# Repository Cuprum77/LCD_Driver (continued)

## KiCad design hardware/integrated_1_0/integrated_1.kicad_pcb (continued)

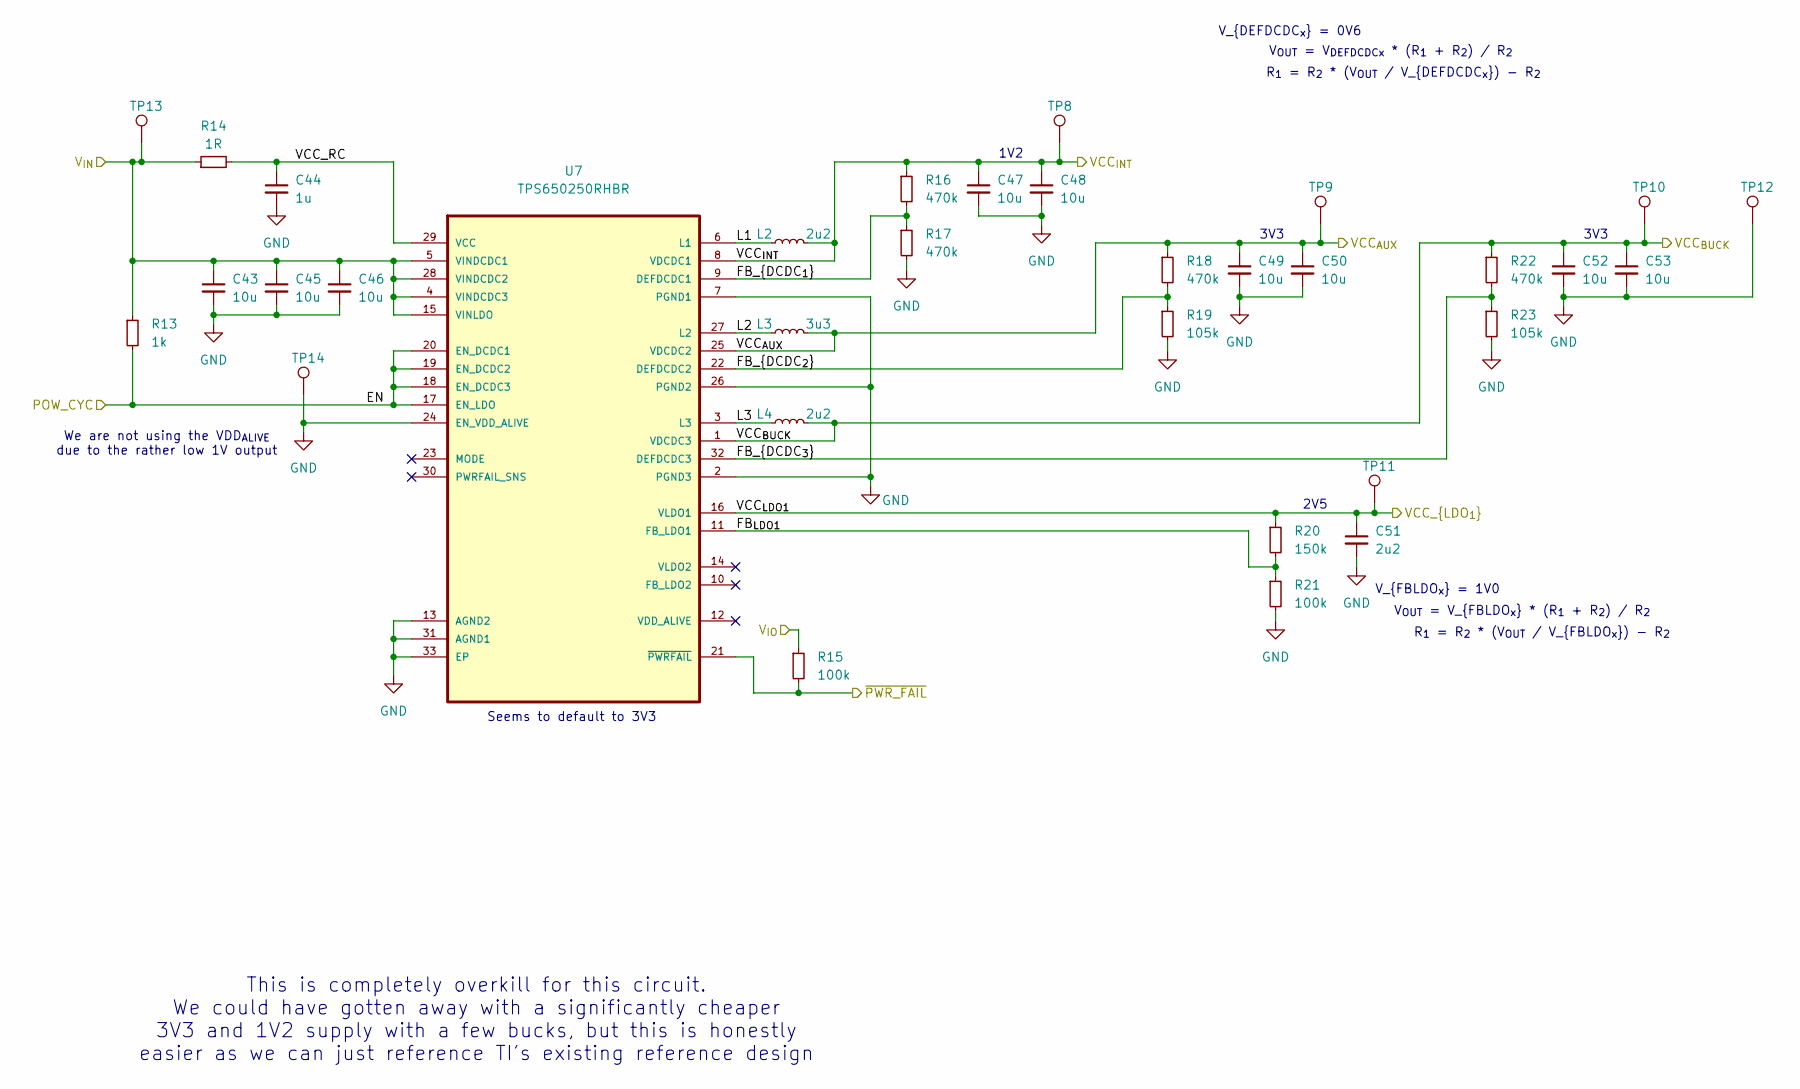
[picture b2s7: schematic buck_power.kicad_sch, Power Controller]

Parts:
C43, C45, C46, C47, C48, C49, C50, C52, C53: 10u; C_0603_1608Metric
C44: 1u; C_0402_1005Metric
C51: 2u2; C_0603_1608Metric
L2, L4: 2u2; XRNR4012
L3: 3u3; XRNR4012
R13: 1k; R_0402_1005Metric
R14: 1R; R_0402_1005Metric
R15, R21: 100k; R_0402_1005Metric
R16, R17, R18, R22: 470k; R_0402_1005Metric
R19, R23: 105k; R_0402_1005Metric
R20: 150k; R_0402_1005Metric
TP8, TP9, TP10, TP11, TP12, TP13, TP14: TestPoint; TestPoint_Pad_D1.0mm
U7: TPS650250RHBR; IC_ADS125H01IRHBT

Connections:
+2V5: C51.1, R20.1, TP11.1, U7.16 (VLDO1); also elsewhere on the board
+3V3: C52.1, C53.1, L4.2, R15.1, R22.1, TP10.1, U7.1 (VDCDC3); also elsewhere on the board
+5V: C43.1, C45.1, C46.1, R13.1, R14.1, TP13.1, U7.4 (VINDCDC3), U7.5 (VINDCDC1), U7.15 (VINLDO), U7.28 (VINDCDC2); also elsewhere on the board
/Buck Converter/EN: R13.2, U7.17 (EN_LDO), U7.18 (EN_DCDC3), U7.19 (EN_DCDC2), U7.20 (EN_DCDC1); also elsewhere on the board
/Buck Converter/FB_{DCDC_{1}}: R16.2, R17.1, U7.9 (DEFDCDC1)
/Buck Converter/FB_{DCDC_{2}}: R18.2, R19.1, U7.22 (DEFDCDC2)
/Buck Converter/FB_{DCDC_{3}}: R22.2, R23.1, U7.32 (DEFDCDC3)
/Buck Converter/FB_{LDO1}: R20.2, R21.1, U7.11 (FB_LDO1)
/Buck Converter/L1: L2.1, U7.6 (L1)
/Buck Converter/L2: L3.1, U7.27 (L2)
/Buck Converter/L3: L4.1, U7.3 (L3)
/Buck Converter/VCC_RC: C44.1, R14.2, U7.29 (VCC)
/Buck Converter/~PWR_FAIL: R15.2, U7.21 (~PWRFAIL); also elsewhere on the board
/VCC_{AUX}: C49.1, C50.1, L3.2, R18.1, TP9.1, U7.25 (VDCDC2); also elsewhere on the board
/VCC_{INT}: C47.1, C48.1, L2.2, R16.1, TP8.1, U7.8 (VDCDC1); also elsewhere on the board
GND: C43.2, C44.2, C45.2, C46.2, C47.2, C48.2, C49.2, C50.2, C51.2, C52.2, C53.2, R17.2, R19.2, R21.2, R23.2, TP12.1, TP14.1, U7.2 (PGND3), U7.7 (PGND1), U7.13 (AGND2), U7.24 (EN_VDD_ALIVE), U7.26 (PGND2), U7.31 (AGND1), U7.33 (EP), U7.34 (EP), U7.35 (EP), U7.36 (EP), U7.37 (EP), U7.38 (EP); also elsewhere on the board

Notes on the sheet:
V_{DEFDCDC_{x}} = 0V6
Seems to default to 3V3
R_{1} = R_{2} * (V_{OUT} / V_{DEFDCDC_{x}}) - R_{2}
3V3
2V5
V_{FBLDO_{x}} = 1V0
V_{OUT} = V_{FBLDO_{x}} * (R_{1} + R_{2}) / R_{2}
This is completely overkill for this circuit. We could have gotten away with a significantly cheaper 3V3 and 1V2 supply with a few bucks, but this is honestly easier as we can just reference TI's existing reference design
R_{1} = R_{2} * (V_{OUT} / V_{FBLDO_{x}}) - R_{2}
V_{OUT} = V_{DEFDCDCx} * (R_{1} + R_{2}) / R_{2}
We are not using the VDD_{ALIVE} due to the rather low 1V output
3V3
1V2

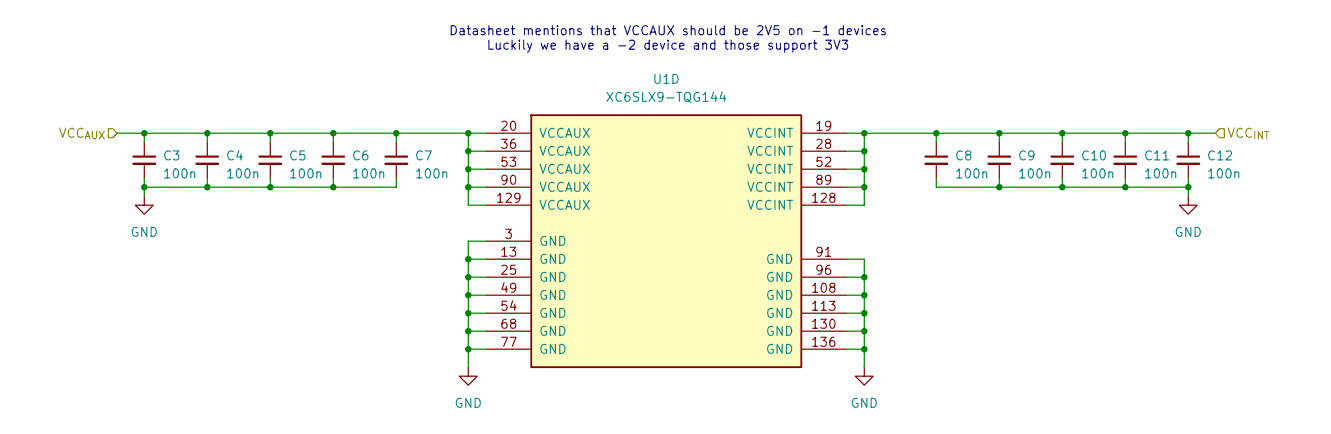
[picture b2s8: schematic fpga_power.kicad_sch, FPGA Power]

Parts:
C3, C4, C5, C6, C7, C8, C9, C10, C11, C12: 100n; C_0402_1005Metric
U1: XC6SLX9-TQG144; TQFP-144_20x20mm_P0.5mm

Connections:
/VCC_{AUX}: C8.1, C9.1, C10.1, C11.1, C12.1, U1.19 (VCCINT), U1.28 (VCCINT), U1.52 (VCCINT), U1.89 (VCCINT), U1.128 (VCCINT); also elsewhere on the board
/VCC_{INT}: C3.1, C4.1, C5.1, C6.1, C7.1, U1.20 (VCCAUX), U1.36 (VCCAUX), U1.53 (VCCAUX), U1.90 (VCCAUX), U1.129 (VCCAUX); also elsewhere on the board
GND: C3.2, C4.2, C5.2, C6.2, C7.2, C8.2, C9.2, C10.2, C11.2, C12.2, U1.3 (GND), U1.13 (GND), U1.25 (GND), U1.49 (GND), U1.54 (GND), U1.68 (GND), U1.77 (GND), U1.91 (GND), U1.96 (GND), U1.108 (GND), U1.113 (GND), U1.130 (GND), U1.136 (GND); also elsewhere on the board

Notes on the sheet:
Datasheet mentions that VCCAUX should be 2V5 on -1 devices Luckily we have a -2 device and those support 3V3

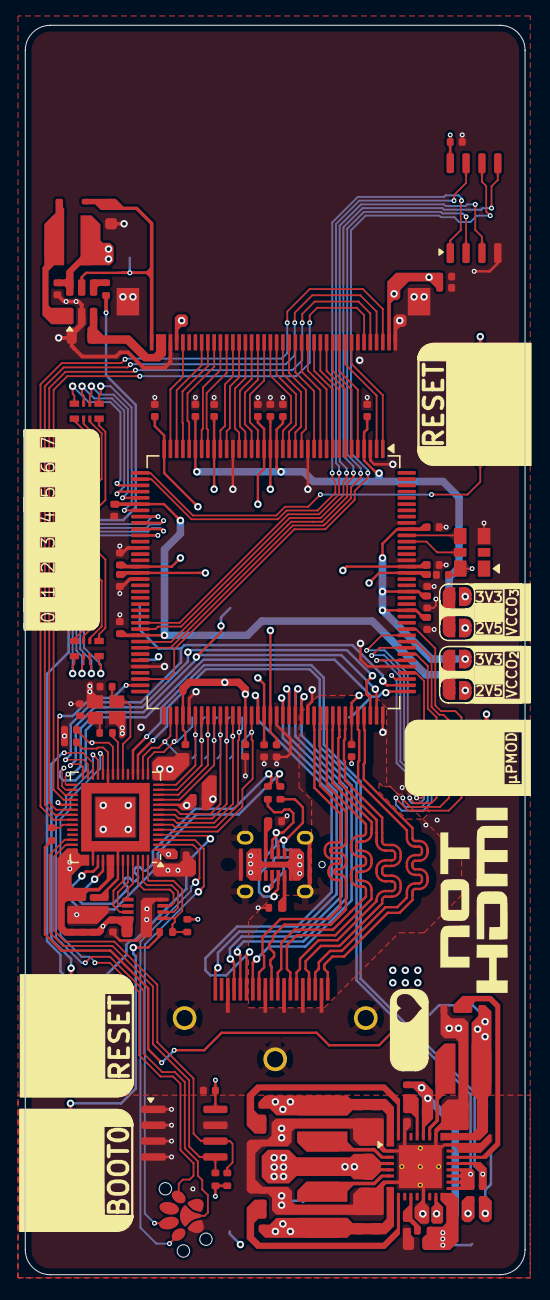
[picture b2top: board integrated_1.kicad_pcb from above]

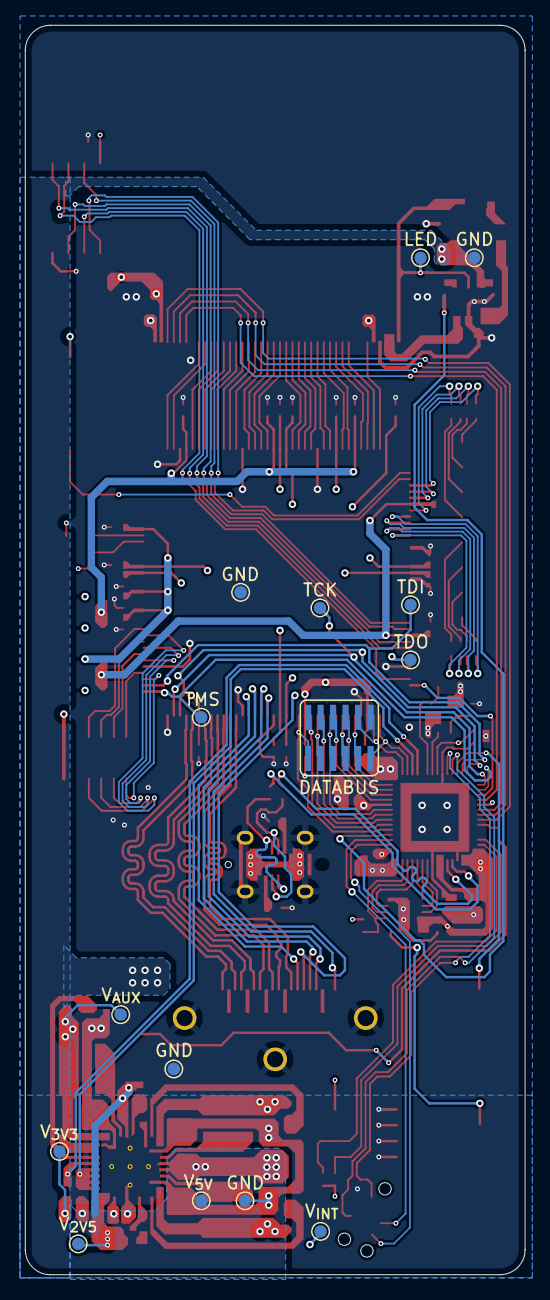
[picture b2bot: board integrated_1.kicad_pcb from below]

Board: 4 copper layers, 40.0 x 100.0 mm, 129 parts (15 on the bottom side), 141 nets.

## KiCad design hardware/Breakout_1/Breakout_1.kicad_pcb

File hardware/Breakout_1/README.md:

# Breakout Board
Note, this is not a complete project. It lacks the necessary files to properly modify the design. This is purely out of the fact that this is a prototype and I am too lazy to properly document it.

This repo contains the KiCAD files for the first iteration of this project, the breakout board.

## Known Issues

These are the known issues with the current design:
- No pull-up resistors on the I2C lines
- No reset button
- No ability to power the board from the USB port (for the microcontroller)
- Difficult to add external power to the board
- More ground connections!
- Boost Converter is not capable of providing enough current for the display. Does not match the chips rated output.

## 3D Files

In the [3D](./3d/) folder you can find the 3D models for the board and a stand for the display to rest on.
The [stand](./3d/stand.stl) is a very crude design. It may not be very printable, but it works well enough for a prototype. 

This will not be developed further as there will not be a need for it in the final design.

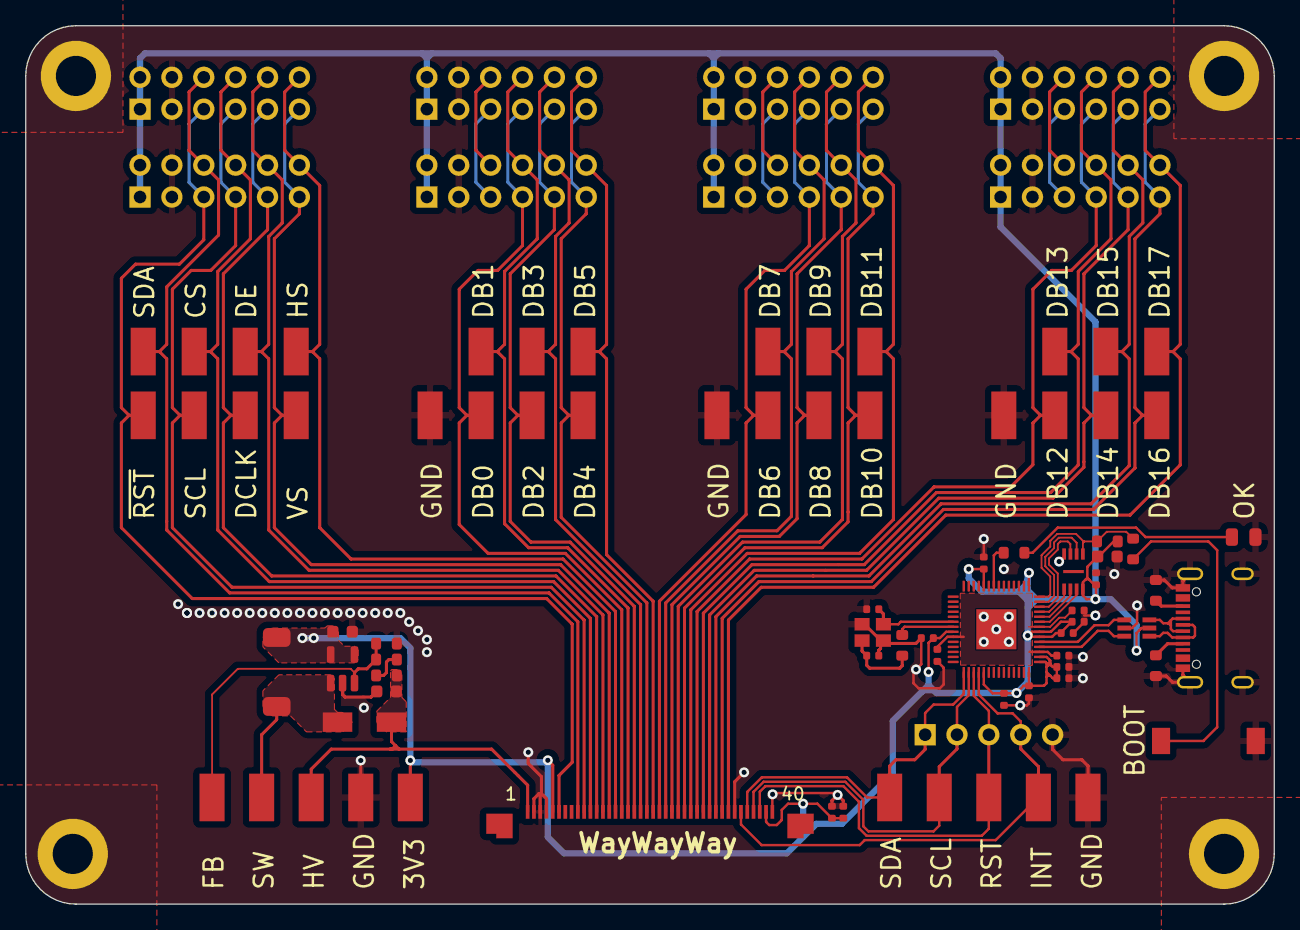
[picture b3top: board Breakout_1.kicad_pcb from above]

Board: 2 copper layers, 99.5 x 70.0 mm, 87 parts (0 on the bottom side), 61 nets.

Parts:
C1, C12, C22: 1u; C_0402_1005Metric
C2, C6, C9, C10, C13, C14, C15, C16, C17, C18, C19: 100n; C_0402_1005Metric
C3: 1u; C_0603_1608Metric
C4, C5: 8p; C_0402_1005Metric
C7: 10u; C_0603_1608Metric
C8: 2u2; C_0603_1608Metric
D1: LED; D_0805_2012Metric
D2: SS14; DIOM5227X270N
DS1: ST7701_IPS_3.99_TOUCH; AMPHENOL_F32Q-1A7H1-11040
J1, J2, J3, J4: Conn_01x12; PinHeader_2x06_P2.54mm_Horizontal
J5, J6, J7, J8: Conn_01x12; PinHeader_2x06_P2.54mm_Vertical
J9: USB4105-GF-A-120; USB_C_Receptacle_GCT_USB4105-xx-A_16P_TopMnt_Horizontal
J10: Conn_01x05; PinHeader_1x05_P2.54mm_Vertical
L1: 10u; L_TDK_SLF6045
R1, R2: 5k1; R_0603_1608Metric
R3: 270; R_0603_1608Metric
R4: 10K; R_0603_1608Metric
R5: DNF; R_0603_1608Metric
R6: 1k; R_0603_1608Metric
R7, R9: 1M; R_0603_1608Metric
R8: 105k; R_0603_1608Metric
SW1: DNF; PTS636 SM25J SMTR LFS
TP1, TP4, TP5, TP6, TP7, TP8, TP9, TP10, TP11, TP12, TP13, TP14, TP15, TP16, TP17, TP18, TP19, TP20, TP21, TP22, TP23, TP24, TP25, TP26, TP27, TP28, TP29, TP30, TP31, TP32, TP33, TP34, TP35, TP36, TP37, TP38, TP39, TP40, TP41: TestPoint; TestPoint_Keystone_5019_Minature_No_Silkscreen
U1: AP3015; SOT-23-5
U2: W25Q16JV; W25Q16JVUXIQ TR
U3: USBUF02W6; SOT65P210X110-6N
U4: RP2040; QFN-56-1EP_7x7mm_P0.4mm_EP3.2x3.2mm
Y1: 12MHz; ECS120836CKMTR3

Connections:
+1V1: C9.1, C10.1, C12.1, U4.23 (DVDD), U4.45 (VREG_VOUT), U4.50 (DVDD)
+3V3: C1.1, C2.1, C6.1, C7.1, C8.1, C13.1, C14.1, C15.1, C16.1, C17.1, C18.1, C19.1, C22.1, DS1.5 (VCC), DS1.39 (TP_VCC), J1.1, J1.2, J2.1, J2.2, J3.1, J3.2, J4.1, J4.2, J5.1, J5.2, J6.1, J6.2, J7.1, J7.2, J8.1, J8.2, L1.1, R5.2, TP34.1, U1.4 (~SHDN), U1.5 (VIN), U2.8 (VCC), U3.5 (3V3), U4.1 (IOVDD), U4.10 (IOVDD), U4.22 (IOVDD), U4.33 (IOVDD), U4.42 (IOVDD), U4.43 (ADC_AVDD), U4.44 (VREG_IN), U4.48 (USB_VDD), U4.49 (IOVDD)
/CS: DS1.11 (CS), J1.8, J5.8, TP7.1
/DB0: DS1.16 (DB0), J2.7, J6.7, TP12.1
/DB1: DS1.17 (DB1), J2.8, J6.8, TP13.1
/DB2: DS1.18 (DB2), J2.9, J6.9, TP14.1
/DB3: DS1.19 (DB3), J2.10, J6.10, TP15.1
/DB4: DS1.20 (DB4), J2.11, J6.11, TP16.1
/DB5: DS1.21 (DB5), J2.12, J6.12, TP17.1
/DB6: DS1.22 (DB6), J3.7, J7.7, TP18.1
/DB7: DS1.23 (DB7), J3.8, J7.8, TP19.1
/DB8: DS1.24 (DB8), J3.9, J7.9, TP20.1
/DB9: DS1.25 (DB9), J3.10, J7.10, TP21.1
/DB10: DS1.26 (DB10), J3.11, J7.11, TP22.1
/DB11: DS1.27 (DB11), J3.12, J7.12, TP23.1
/DB12: DS1.28 (DB12), J4.7, J8.7, TP24.1
/DB13: DS1.29 (DB13), J4.8, J8.8, TP25.1
/DB14: DS1.30 (DB14), J4.9, J8.9, TP26.1
/DB15: DS1.31 (DB15), J4.10, J8.10, TP27.1
/DB16: DS1.32 (DB16), J4.11, J8.11, TP28.1
/DB17: DS1.33 (DB17), J4.12, J8.12, TP29.1
/DCLK: DS1.12 (DCLK), J1.9, J5.9, TP8.1
/DE: DS1.13 (DE), J1.10, J5.10, TP9.1
/FB: R8.1, R9.2, TP40.1, U1.3 (FB)
/HS: DS1.15 (HS), J1.12, J5.12, TP11.1
/LEDA: C3.1, D2.1 (K), DS1.1 (LEDA), R7.1, TP1.1
/Microcontroller/LED_STATUS: R3.2, U4.8 (GPIO6)
/Microcontroller/QSPI_SCLK: U2.6 (CLK), U4.52 (QSPI_SCLK)
/Microcontroller/QSPI_SD0: U2.5 (DI(IO0)), U4.53 (QSPI_SD0)
/Microcontroller/QSPI_SD1: U2.2 (DO(IO1)), U4.55 (QSPI_SD1)
/Microcontroller/QSPI_SD2: U2.3 (IO2), U4.54 (QSPI_SD2)
/Microcontroller/QSPI_SD3: U2.7 (IO3), U4.51 (QSPI_SD3)
/Microcontroller/QSPI_SS: R4.1, R5.1, U2.1 (~CS), U4.56 (QSPI_SS)
/Microcontroller/USB_D+: U3.1 (D+), U4.47 (USB_DP)
/Microcontroller/USB_D-: U3.3 (D-), U4.46 (USB_DM)
/Microcontroller/USB_DR+: J9.A6 (D+), J9.B6 (D+), U3.6 (D+)
/Microcontroller/USB_DR-: J9.A7 (D-), J9.B7 (D-), U3.4 (D-)
/Microcontroller/XIN: C4.2, U4.20 (XIN), Y1.1
/Microcontroller/XOUT: R6.1, U4.21 (XOUT)
/Microcontroller/XOUT_R: C5.2, R6.2, Y1.3
/SCL: DS1.10 (SCL), J1.7, J5.7, TP6.1
/SDA: DS1.9 (SDA), J1.6, J5.6, TP5.1
/SWITCH: D2.2 (A), L1.2, TP41.1, U1.1 (SW)
/TP_INT: DS1.35 (TP_INT), J10.4, TP30.1, U4.32 (GPIO21)
/TP_RST: DS1.38 (TP_RST), J10.3, TP33.1, U4.31 (GPIO20)
/TP_SCL: DS1.37 (TP_SCL), J10.2, TP32.1, U4.30 (GPIO19)
/TP_SDA: DS1.36 (TP_SDA), J10.1, TP31.1, U4.29 (GPIO18)
/VS: DS1.14 (VS), J1.11, J5.11, TP10.1
/~RST: DS1.6 (~RST), J1.5, J5.5, TP4.1
GND: C1.2, C2.2, C3.2, C4.1, C5.1, C6.2, C7.2, C8.2, C9.2, C10.2, C12.2, C13.2, C14.2, C15.2, C16.2, C17.2, C18.2, C19.2, C22.2, D1.1 (K), DS1.2 (LEDK1), DS1.3 (LEDK2), DS1.4 (GND), DS1.34 (GND), DS1.40 (GND), J1.3, J1.4, J2.3, J2.4, J3.3, J3.4, J4.3, J4.4, J5.3, J5.4, J6.3, J6.4, J7.3, J7.4, J8.3, J8.4, J9.A1 (GND), J9.A12 (GND), J9.B1 (GND), J9.B12 (GND), J9.S1 (SHIELD), J10.5, R1.1, R2.1, R8.2, SW1.1, TP35.1, TP36.1, TP37.1, TP38.1, TP39.1, U1.2 (GND), U2.4 (GND), U3.2 (Grd), U4.57 (GND), Y1.2, Y1.4
unnamed: D1.2 (A), R3.1
unnamed: J2.5, J6.5
unnamed: J2.6, J6.6
unnamed: J3.5, J7.5
unnamed: J3.6, J7.6
unnamed: J4.5, J8.5
unnamed: J4.6, J8.6
unnamed: J9.A5 (CC1), R1.2
unnamed: J9.B5 (CC2), R2.2
unnamed: R4.2, SW1.2
unnamed: R7.2, R9.1

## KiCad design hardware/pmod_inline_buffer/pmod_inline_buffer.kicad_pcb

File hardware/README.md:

# Hardware

This repo contains the KiCAD files for the current hardware prototypes of the LCD driver board.

## Current version

The latest board manufactured is the [Breakout_1](Breakout_1/) board. This PCB is a breakout board for the LCD display, which allows for easy testing and verification of the display. It also contains a 40 pin header for the LCD display itself and a PMOD interface for hooking up with a FPGA board.

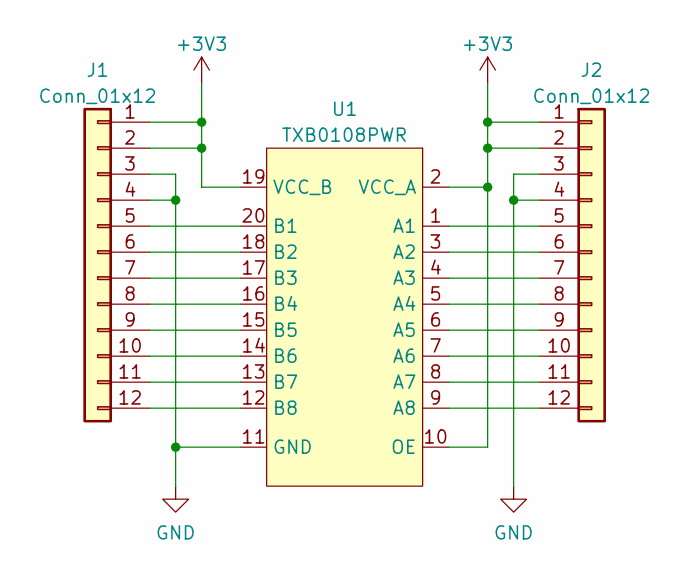
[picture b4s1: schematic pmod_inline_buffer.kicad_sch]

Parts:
J1: Conn_01x12; PinHeader_2x06_P2.54mm_Horizontal
J2: Conn_01x12; PinSocket_2x06_P2.54mm_Horizontal
U1: TXB0108PWR; TSSOP-20_4.4x6.5mm_P0.65mm

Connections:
+3V3: J1.1, J1.2, J2.1, J2.2, U1.2 (VCC_A), U1.10 (OE), U1.19 (VCC_B)
GND: J1.3, J1.4, J2.3, J2.4, U1.11 (GND)
unnamed: J1.5, U1.20 (B1)
unnamed: J1.6, U1.18 (B2)
unnamed: J1.7, U1.17 (B3)
unnamed: J1.8, U1.16 (B4)
unnamed: J1.9, U1.15 (B5)
unnamed: J1.10, U1.14 (B6)
unnamed: J1.11, U1.13 (B7)
unnamed: J1.12, U1.12 (B8)
unnamed: J2.5, U1.1 (A1)
unnamed: J2.6, U1.3 (A2)
unnamed: J2.7, U1.4 (A3)
unnamed: J2.8, U1.5 (A4)
unnamed: J2.9, U1.6 (A5)
unnamed: J2.10, U1.7 (A6)
unnamed: J2.11, U1.8 (A7)
unnamed: J2.12, U1.9 (A8)

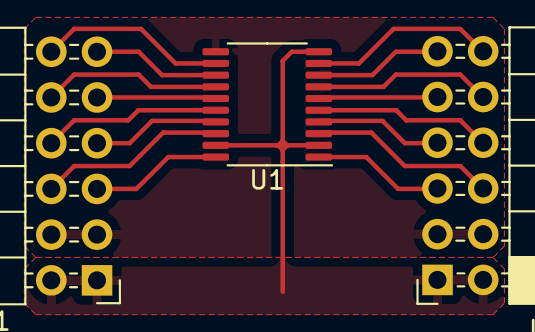
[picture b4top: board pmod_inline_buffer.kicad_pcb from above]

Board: 2 copper layers, 3 parts (0 on the bottom side), 18 nets.

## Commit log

2024-01-05 added gitignore
2024-01-05 first breakout board
2024-01-05 regenerated the gerber
2024-01-06 added license and a basic readme
2024-01-06 fixed readme?
2024-01-06 updated git ignore
2024-01-08 added a firmware folder
2024-01-08 added an ibom for breakout1
2024-01-08 spi hardware
2024-01-08 updated the spi to follow university guidelines
2024-01-08 added readme
2024-01-08 fixed some minor typos
2024-01-08 added the assembler for the psuedo assembly code
2024-01-08 updated the main readme
2024-01-08 updated the spi readme with docs
2024-01-08 typo
2024-01-08 improved readability
2024-01-08 simplified the instructionset
2024-01-08 fixed an error in overflow conditions
2024-01-09 fixed the output not taking comments into account
2024-01-09 added the sequencer
2024-01-09 fixed issue with rom and made it more efficient
2024-01-09 fixed a few names
2024-01-09 attempt to remove linguist from picking up ibom
2024-01-09 fixed flaw in readme, added example file
2024-01-09 updated the readme to reflect current state
2024-01-09 removed instructions from showing up, as this is supposed to be a general purpose module
2024-01-09 added a done signal for the top level
2024-01-09 moved the example instruction set to a dedicated folder
2024-01-09 updated readme to reflect changes
2024-01-09 added a missing newline (cosmetics)
2024-01-14 added uvvm as submodule
2024-01-14 replaced uvvm with uvvm_light
2024-01-14 added more readme files
2024-01-14 added simple readme for spi_init tb's
2024-01-14 added compiled uvvm folder gitignore
2024-01-14 added the rgb file with entity only
2024-01-14 added the spi simulation files
2024-01-14 fixed variable names not matching after previous update
2024-01-14 updated the main readme to include the new folders
2024-01-14 fixed bad link
2024-01-14 added the SPI UVVM testbench and relevant files
2024-01-14 updated testbench readmes
2024-01-14 fixed error in the readme
2024-01-14 removed unecessary words
2024-01-14 added default states to avoid simulation problems
2024-01-14 added the sequencer simulation files
2024-01-14 added the new sequencer testbench
2024-01-14 minor corrections of the spi simulation
2024-01-14 saving state
2024-01-14 restructured the project
2024-01-14 rewrote script to work in terminal
2024-01-14 removed unused files
2024-01-14 re-included accidently removed uvvm_light
2024-01-14 further restructuring
2024-01-14 correcting a typo
2024-01-14 removed unecessary files
2024-01-14 fixing wrong case leftover from restructuring
2024-01-14 updated the readme's to reflect changes
2024-01-14 updated more files to match the lowercase structure
2024-01-14 fixed the gitignore
2024-01-14 added known issues to the pcb page
2024-01-14 added information for the chipset used for touch
2024-01-14 added minimally functional library
2024-01-15 added rgb file
2024-01-15 added the top file
2024-01-15 minor spelling mistakes
2024-01-15 fixed a few things and added the sim file
2024-01-15 added a brief description to the RGB controller simulation
2024-01-15 fixed minor bugs
2024-01-16 added a resetter module
2024-01-16 updated project to reflect addition of resetter module
2024-01-16 added vivado project
2024-01-16 attempt 2 at the instructions
2024-01-16 added the ability to reset the heart
2024-01-16 gave the top a new heart
2024-01-16 updated formatting to match rest of project
2024-01-16 updated to make it not count generated hdl files
2024-01-16 updated to ignore all generated files (hopefully)
2024-01-16 updated again
2024-01-16 more readmes
2024-01-17 added an alternative d/c mode
2024-01-17 added the alternative d/c mode to the sequencer
2024-01-17 lowercase name
2024-01-17 crude start
2024-01-17 fixed minor typo
2024-01-21 added ability to invert the D/C bit from top-level
2024-01-21 re-ran the synthesis
2024-01-21 appended readme
2024-01-21 fixed a bad link
2024-01-21 passed variables up, fixed de signal fault
2024-01-21 updated tb to reflect changes
2024-01-21 updated top file to reflect changes, added a simple test pattern
2024-01-21 minor changes
2024-01-21 added digilent repo as a submodule
2024-01-21 fixed a spelling mistake
2024-01-21 fixed the naming in the uvvm code
2024-01-21 modified top to accept hdmi
2024-01-21 generic xilinx trash
2024-01-21 rgb sim rerun (new file)
2024-01-22 reverted to integrated ddc for the time being
2024-01-22 regenerated files
2024-01-22 added ddc files
2024-01-22 removed ddc, didnt work as hoped
2024-01-22 functional hdmi prototype
2024-01-23 cleanup, removed unused variables
2024-01-26 added the edid data needed to make it plug'n'play
2024-01-26 replaced bad link
2024-01-26 rewritten for consistency
2024-01-26 fixed spaces
2024-01-26 created a step file
2024-01-26 added the stand model
2024-01-26 renamed the folder to fit the restructuring (part 2)
2024-01-26 removed old folder
2024-01-26 updated the zybo readme
2024-01-26 updated the readme to reflect changes
2024-01-27 temporarily ignore doxy files
2024-01-27 moved the rom generator
2024-01-27 moved the rom generator and rewrote the python script
2024-01-27 removed to-be-rewritten files
2024-01-27 moved the datasheets
2024-01-27 removed unused code
2024-01-27 moved the software files
2024-01-27 added work in progress files
2024-01-27 renamed the simulation folder to match project layout
2024-01-27 crude update of main readme
2024-01-27 fixed broken links
2024-01-27 removed unused tb
2024-01-27 file has been cleaned, and unecessary parts removed
2024-01-27 simulation has been updated to reflect changes in the spi file
2024-01-27 fixed the wrong type error in the rom file output
2024-01-27 updated to utilize records
2024-01-27 functional update
2024-01-30 regenerated the pll module
2024-01-30 renamed top module in vivado to match filename
2024-01-30 changed entity name to match filename
2024-01-30 added touch position data readout
2024-01-30 updated comments
2024-01-30 keep the binary
2024-02-11 completed the touch library, added interrupts to fetch new data
2024-02-11 added crude start to the usb handling code
2024-02-11 microcontroller will now report the commit hash as its version number
2024-02-11 just vsc things
2024-02-11 main changed to pure C, some rudimentary code added
2024-02-11 current build, may not work
2024-02-23 updated kicad files to 8.0.0
2024-02-23 added some info to readme
2024-02-23 updated schematic files to kicad 8.0.0
2024-02-23 updated sheet file to kicad 8.0.0
2024-02-23 added bom file
2024-02-23 updated readme again
2024-02-24 added programming script to speed up development
2024-03-01 added touch descriptor
2024-03-01 removed leftover include
2024-03-01 replaced the touch structs
2024-03-01 added meme descriptor and support for new touch interface
2024-03-01 moved tinyusb cbs to usb_device.c, changed to work on Pico for rapid prototyping
2024-03-01 updated readme to reflect source for some code
2024-03-01 commented out non-essentials
2024-03-01 updated to reflect usb_device.c changes
2024-03-02 added macro for point count to remove a few hard values
2024-03-02 updated to only read if ready, fixing missing status register
2024-03-02 vsc junk
2024-03-08 the solution came to me in a dream
2024-03-08 shotgun method of bug solving (didnt work)
2024-03-11 added the work in progress second pcb
2024-03-11 renaming a few pins
2024-03-11 added a readme
2024-03-11 added some more information to the readme
2024-03-22 seperated converter from fpga power sheet
2024-03-22 added a buck converter
2024-03-22 moved usb resistors inside the rp2040 sheet
2024-03-22 automatic kicad reference update
2024-03-22 hooked up dvi and rp2040 to fpga
2024-03-22 hooked up display to fpga
2024-03-22 updated gitignore with kicad plugin
2024-03-22 added top level connections between the fpga modules
2024-03-22 added more relevant documentation
2024-03-22 created a rudementary shape and added a few parts and tracks to visualize pcb
2024-03-23 rearranged the pinout to make more sense
2024-03-24 reannotated schematic
2024-03-24 started the layout process + added new hdmi and usb connectors
2024-04-04 reannotated
2024-04-04 added cheap eeprom
2024-04-04 added async reset
2024-04-04 added leds
2024-04-04 removed gpio references
2024-04-04 added sources for silkscreen "art"
2024-04-04 added more potentially useful datasheets
2024-04-04 created a rough 3d model of the display for improved visualization
2024-04-04 improved top level visually
2024-04-04 kicad data that keeps changing by a few variables every time
2024-04-04 significant progress in the layout has been made, close to completion
2024-04-05 finalizing the schematic and layout
2024-04-11 added testpoints
2024-04-19 exported 3d models + added date stamp
2024-04-19 removed depreciated files
2024-04-19 changed active layer
2024-04-22 fixed critical issue - display connector was mirrored
2024-04-22 added ibom
2024-05-05 adding the kicad-render script
2024-05-05 saving the drc violation exclusions
2024-05-05 adding the breakout board images
2024-05-05 fixed yaml formatting error
2024-05-05 attempt to fix yaml error in github actions #2
2024-05-05 fixed url
2024-06-20 pushed readme update featuring design error
2024-06-27 renamed the revision 1 of the integrated solution to integrated_1_0
2024-06-27 created a revision 1.1 of the pcb design
2024-06-28 implemented changes as suggested by https://github.com/diminDDL
2024-06-28 added ISE specific source files, split up the vivado and ise to avoid compatibility issues
2024-06-28 edid subdirectory makeover, including scripts specific for ISE
2024-06-28 README update
2024-06-28 updated the readmes by removing outdated information and updating images
2024-06-28 added a readme for the newest pcb
2024-06-28 included bitfiles as well as the missing constraint file
2024-06-28 minor changes in the readme with some more details
2024-06-28 changed copper pour to not have thermal reliefs (it looked nicer)
